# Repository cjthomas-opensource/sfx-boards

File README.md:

# Chris's Special-Effects Boards

## Overview

These are a series of hobby-project boards intended to produce sounds and
blinking lights. The boards are Arduino-compatible and small enough to be
packaged inside homemade toys.

Except where indicated otherwise, the files in this project are copyright (c)
2025 by Christopher Thomas and are released under the Creative Commons
Attribution-ShareAlike 4.0 International License.

**FIXME** - This really needs a user manual.

**FIXME** - Firmware code not yet folded into the repository.

## KiCad Configuration

In `Preferences`->`Configure Paths`, set `KICAD_EXT_VENDOR` to point to the
`vendor-kicad` folder.

## Folders

* `pcb-202009-9v` -- Compact board that sits on top of a 9v battery.
Needs an external clock to be programmed. Made with the "`pcb`" program
(now part of `gEDA`) rather than with KiCad.
* `pcb-202502` -- Feature-rich board with terminal block connections. Bulky
and very expensive. Made with KiCad.
* `vendor-datasheets` -- Datasheets. Under vendor copyright.
* `vendor-kicad` -- Vendor-supplied KiCad files, with additions and
modifications where appropriate. Under vendor copyright.
* `vendor-models` -- Vendor-supplied geometry models. Under vendor copyright.

## Gallery

### 2020 Board:

### 2025 Board:

*This is the end of the file.*

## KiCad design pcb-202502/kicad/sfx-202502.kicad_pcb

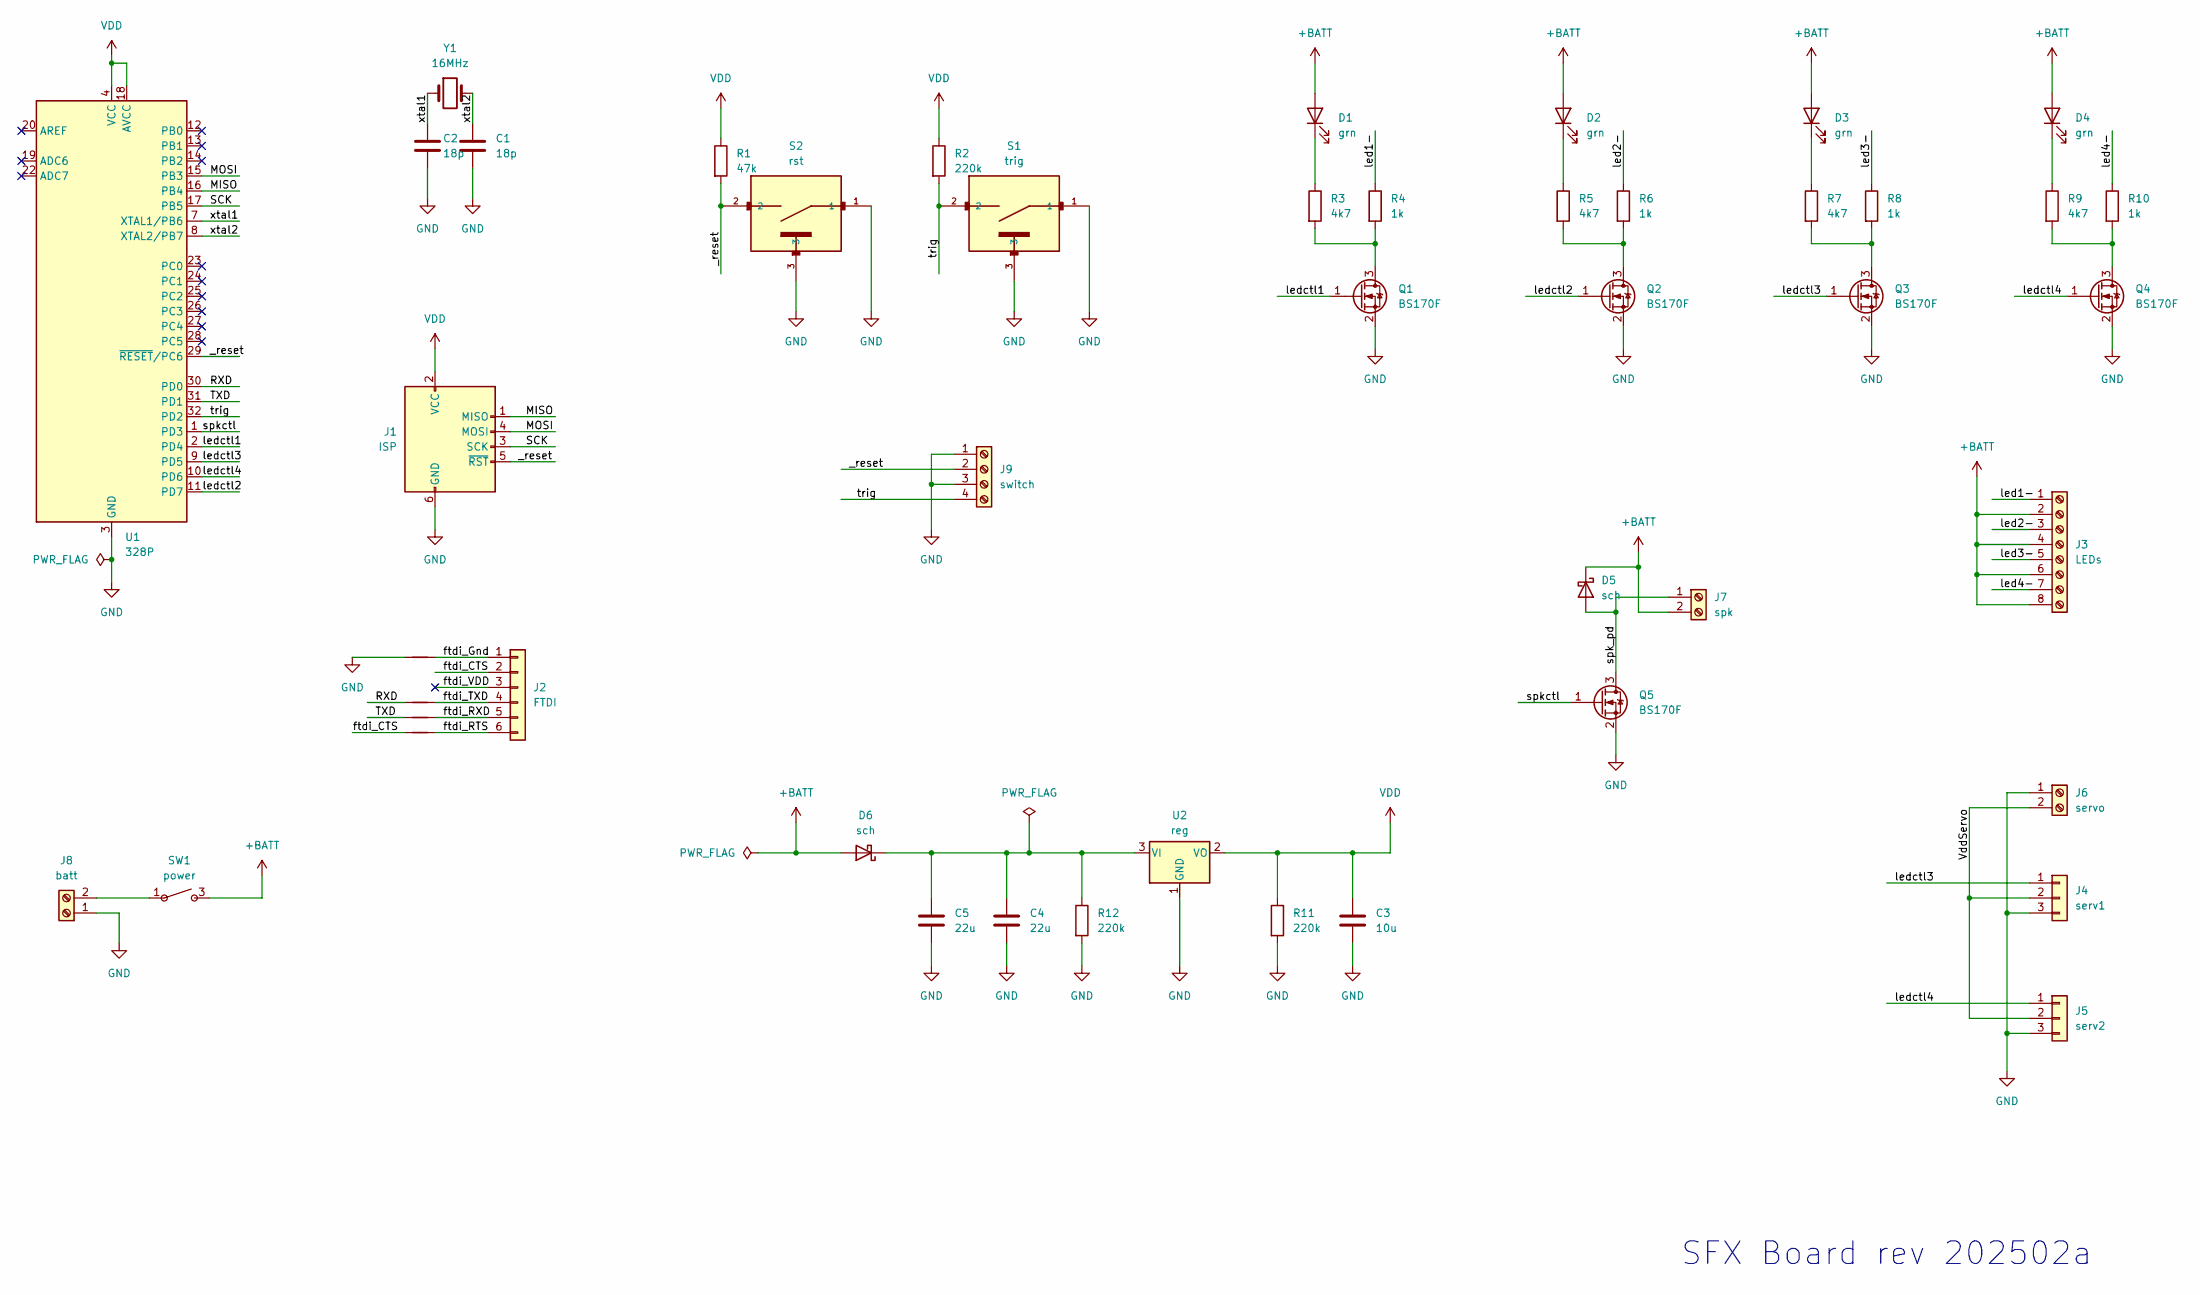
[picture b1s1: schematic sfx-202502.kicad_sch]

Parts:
C1, C2: 18p; C_0805_2012Metric_Pad1.18x1.45mm_HandSolder; MfgPart C0805C180K5GACTU
C3: 10u; C_1206_3216Metric_Pad1.33x1.80mm_HandSolder; MfgPart CC1206KKX7R8BB106
C4, C5: 22u; C_1206_3216Metric_Pad1.33x1.80mm_HandSolder; MfgPart CC1206KFX5R8BB226
D1, D2, D3, D4: grn; LED_0805_2012Metric_Pad1.15x1.40mm_HandSolder; MfgPart APT2012ZGC
D5, D6: sch; D_0805_2012Metric_Pad1.15x1.40mm_HandSolder; MfgPart SD0805S040S0R5
J1: ISP; IDC-Header_2x03_P2.54mm_Vertical; MfgPart 1761681-1
J2: FTDI; PinHeader_1x06_P2.54mm_Horizontal; MfgPart 103906-5
J3: LEDs; TerminalBlock_TE_282834-8_1x08_P2.54mm_Horizontal; MfgPart 282834-8
J4: serv1; PinHeader_1x03_P2.54mm_Horizontal; MfgPart 103906-2
J5: serv2; PinHeader_1x03_P2.54mm_Horizontal; MfgPart 103906-2
J6: servo; TerminalBlock_TE_282834-2_1x02_P2.54mm_Horizontal; MfgPart 282834-2
J7: spk; TerminalBlock_TE_282834-2_1x02_P2.54mm_Horizontal; MfgPart 282834-2
J8: batt; TerminalBlock_TE_282834-2_1x02_P2.54mm_Horizontal; MfgPart 282834-2
J9: switch; TerminalBlock_TE_282834-4_1x04_P2.54mm_Horizontal; MfgPart 282834-4
NT1, NT2, NT3, NT4: NetTie_2; NetTie-2_SMD_Pad0.5mm
Q1, Q2, Q3, Q4, Q5: BS170F; SOT-23_Handsoldering; MfgPart BS170FTA
R1: 47k; R_0805_2012Metric_Pad1.20x1.40mm_HandSolder; MfgPart RC0805FR-0747KL
R2, R11, R12: 220k; R_0805_2012Metric_Pad1.20x1.40mm_HandSolder; MfgPart RC0805FR-07220KL
R3, R5, R7, R9: 4k7; R_0805_2012Metric_Pad1.20x1.40mm_HandSolder; MfgPart RC0805FR-074K7L
R4, R6, R8, R10: 1k; R_0805_2012Metric_Pad1.20x1.40mm_HandSolder; MfgPart RC0805FR-071KL
S1: trig; SW_B3U-1100P; MfgPart B3U-1100P
S2: rst; SW_B3U-1100P; MfgPart B3U-1100P
SW1: power; Switch_Slide_SPST_CK_ES02MCBE; MfgPart ES02MCBE
U1: 328P; TQFP-32_7x7mm_P0.8mm; MfgPart ATMEGA328P-ANR
U2: reg; SOT-23_Handsoldering; MfgPart MCP1703AT-5002E/CB
Y1: 16MHz; Crystal_SMD_HC49-SD_HandSoldering; MfgPart ECS-160-18-5PX-CKM-TR

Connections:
+BATT: D1.2 (A), D2.2 (A), D3.2 (A), D4.2 (A), D5.1 (K), D6.2 (A), J3.2, J3.4, J3.6, J3.8, J7.2, SW1.3 (B), SW1.6 (nc)
/MISO: J1.1 (MISO), U1.16 (PB4)
/MOSI: J1.4 (MOSI), U1.15 (PB3)
/RXD: NT2.1, U1.30 (PD0)
/SCK: J1.3 (SCK), U1.17 (PB5)
/TXD: NT3.1, U1.31 (PD1)
/VddServo: J4.2, J5.2, J6.2
/_reset: J1.5 (~RST), J9.2, R1.2, S2.2, U1.29 (~RESET/PC6)
/ftdi_CTS: J2.2, NT4.1
/ftdi_Gnd: J2.1, NT1.2
/ftdi_RTS: J2.6, NT4.2
/ftdi_RXD: J2.5, NT3.2
/ftdi_TXD: J2.4, NT2.2
/ftdi_VDD: J2.3
/led1-: J3.1, R4.1
/led2-: J3.3, R6.1
/led3-: J3.5, R8.1
/led4-: J3.7, R10.1
/ledctl1: Q1.1 (G), U1.2 (PD4)
/ledctl2: Q2.1 (G), U1.11 (PD7)
/ledctl3: J4.1, Q3.1 (G), U1.9 (PD5)
/ledctl4: J5.1, Q4.1 (G), U1.10 (PD6)
/spk_pd: D5.2 (A), J7.1, Q5.3 (D)
/spkctl: Q5.1 (G), U1.1 (PD3)
/trig: J9.4, R2.2, S1.2, U1.32 (PD2)
/xtal1: C2.1, U1.7 (XTAL1/PB6), Y1.1
/xtal2: C1.1, U1.8 (XTAL2/PB7), Y1.2
GND: C1.2, C2.2, C3.2, C4.2, C5.2, J1.6 (GND), J4.3, J5.3, J6.1, J8.1, J9.1, J9.3, NT1.1, Q1.2 (S), Q2.2 (S), Q3.2 (S), Q4.2 (S), Q5.2 (S), R11.2, R12.2, S1.1, S1.3, S2.1, S2.3, U1.3 (GND), U1.5 (GND), U1.21 (GND), U2.1 (GND)
unnamed: D1.1 (K), R3.1
unnamed: D2.1 (K), R5.1
unnamed: D3.1 (K), R7.1
unnamed: D4.1 (K), R9.1
unnamed: C4.1, C5.1, D6.1 (K), R12.1, U2.3 (VI)
unnamed: Q1.3 (D), R3.2, R4.2
unnamed: Q2.3 (D), R5.2, R6.2
unnamed: Q3.3 (D), R7.2, R8.2
unnamed: Q4.3 (D), R9.2, R10.2
VDD: C3.1, J1.2 (VCC), R1.1, R2.1, R11.1, U1.4 (VCC), U1.6 (VCC), U1.18 (AVCC), U2.2 (VO)

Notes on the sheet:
SFX Board rev 202502a

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
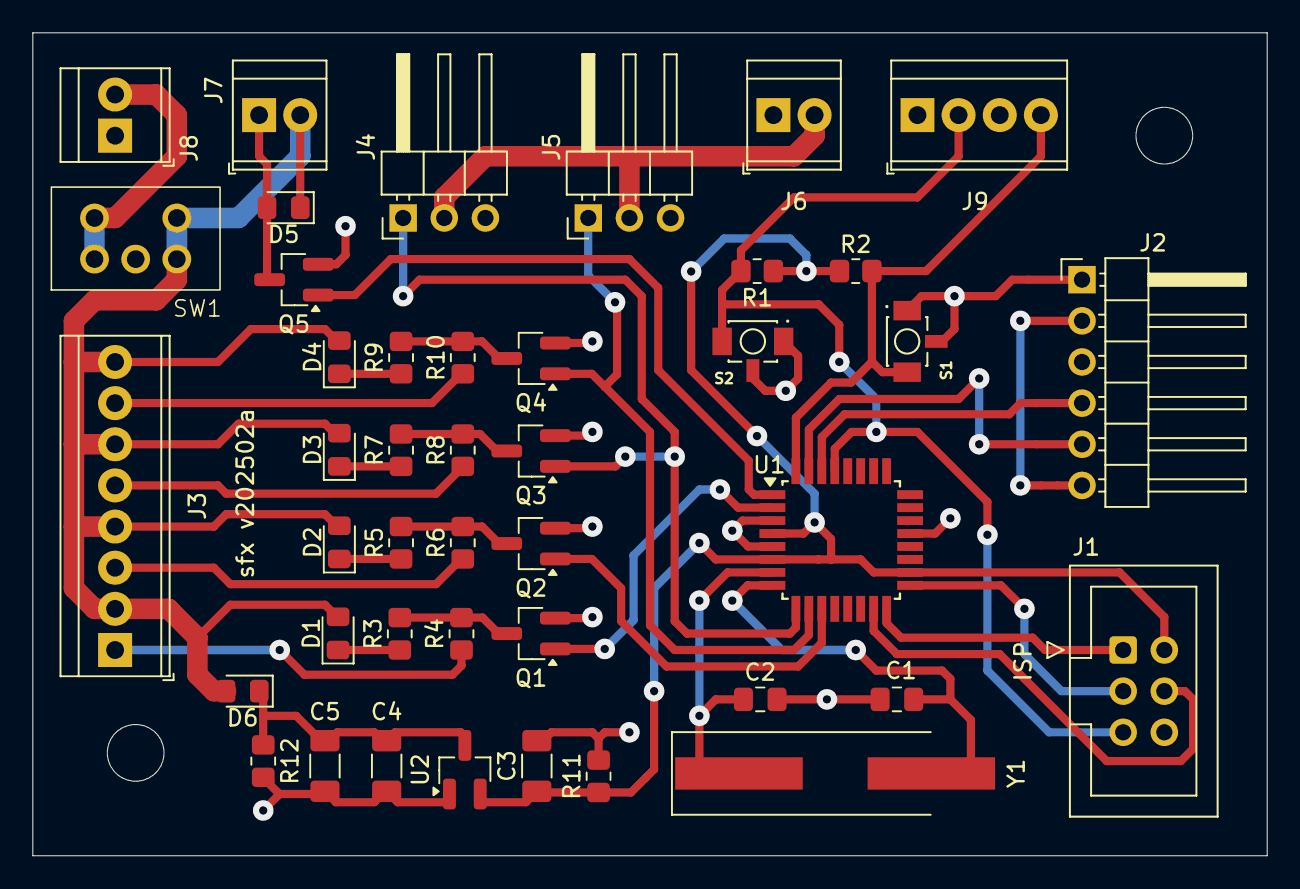
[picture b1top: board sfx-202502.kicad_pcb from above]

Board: 2 copper layers, 76.2 x 50.8 mm, 47 parts (0 on the bottom side), 38 nets.

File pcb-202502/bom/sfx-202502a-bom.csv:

"Reference","Value","Qty","DNP","DkeyPart","MfgPart","Manufacturer"
"C1,C2","18p","2","","399-C0805C180K5GACTUCT-ND","C0805C180K5GACTU","Kemet"
"C3","10u","1","","311-1959-1-ND","CC1206KKX7R8BB106","Yageo"
"C4,C5","22u","2","","13-CC1206KFX5R8BB226CT-ND","CC1206KFX5R8BB226","Yageo"
"D1,D2,D3,D4","grn","4","","754-1438-1-ND","APT2012ZGC","Kingbright"
"D5,D6","sch","2","","478-7802-1-ND","SD0805S040S0R5","Kyocera AVX"
"J1","ISP","1","","A122759-ND","1761681-1","TE Connectivity"
"J2","FTDI","1","","A28630-ND","103906-5","TE Connectivity"
"J3","LEDs","1","","A98338-ND","282834-8","TE Connectivity"
"J4","serv1","1","","A28621-ND","103906-2","TE Connectivity"
"J5","serv2","1","","A28621-ND","103906-2","TE Connectivity"
"J6","servo","1","","A98333-ND","282834-2","TE Connectivity"
"J7","spk","1","","A98333-ND","282834-2","TE Connectivity"
"J8","batt","1","","A98333-ND","282834-2","TE Connectivity"
"J9","switch","1","","A98335-ND","282834-4","TE Connectivity"
"Q1,Q2,Q3,Q4,Q5","BS170F","5","","BS170FCT-ND","BS170FTA","Diodes Incorporated"
"R1","47k","1","","311-47.0KCRCT-ND","RC0805FR-0747KL","Yageo"
"R2,R11,R12","220k","3","","311-220KCRCT-ND","RC0805FR-07220KL","Yageo"
"R3,R5,R7,R9","4k7","4","","311-4.70KCRCT-ND","RC0805FR-074K7L","Yageo"
"R4,R6,R8,R10","1k","4","","311-1.00KCRCT-ND","RC0805FR-071KL","Yageo"
"S1","trig","1","","SW1021CT-ND","B3U-1100P","Omron Electronics"
"S2","rst","1","","SW1021CT-ND","B3U-1100P","Omron Electronics"
"SW1","power","1","","CKN1812-ND","ES02MCBE","CK Components"
"U1","328P","1","","ATMEGA328P-ANRCT-ND","ATMEGA328P-ANR","Atmel"
"U2","reg","1","","MCP1703AT-5002E/CBCT-ND","MCP1703AT-5002E/CB","Microchip Technology"
"Y1","16MHz","1","","50-ECS-160-18-5PX-CKM-CT-ND","ECS-160-18-5PX-CKM-TR","ECS Inc"

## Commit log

2025-08-21 Initial repository. Missing firmware and sound samples.
2025-08-21 Added license.
2025-08-21 Format tweaking in README.
2025-08-22 Added v202502a photos. Tweaked README.
2025-08-22 Fixed capitalization in KiCad.
